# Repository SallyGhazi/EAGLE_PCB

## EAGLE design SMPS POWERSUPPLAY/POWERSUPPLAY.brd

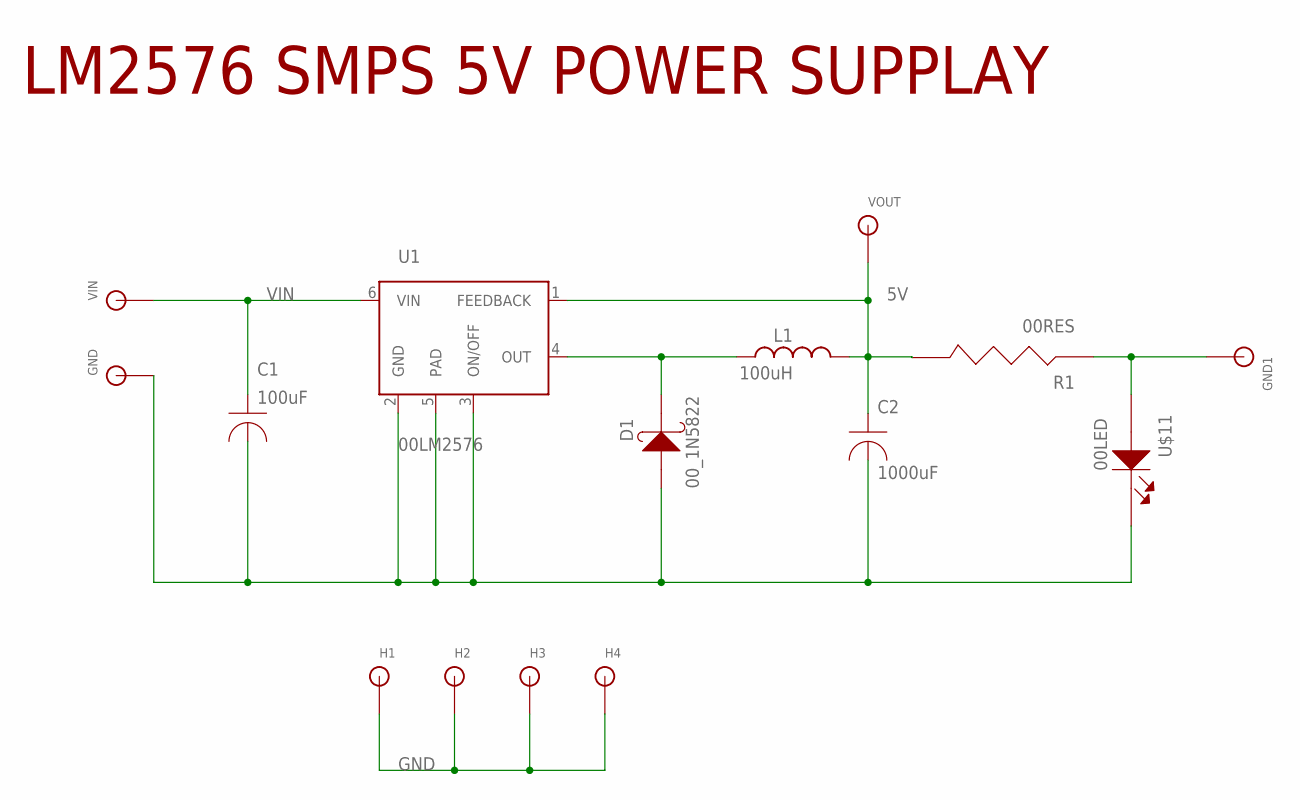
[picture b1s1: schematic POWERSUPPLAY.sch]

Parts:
C1: 100uF; 00CAP
C2: 1000uF; 00CAP
D1: 00_1N5822
GND: 00PAD
GND1: MH_HOLE; 00PAD
H1, H2, H3, H4: MH_HOLE; 00PAD
L1: 100uH; 01INDUCTOR
R1: 00RES
U1: 00LM2576
U$11: 00LED; 0805_LED
VIN: 00PAD
VOUT: MH_HOLE; 00PAD

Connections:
5V: C2.1, L1.2, R1.2, U1.1 (FEEDBACK), VOUT.1
GND: H1.1, H2.1, H3.1, H4.1
unnamed: D1.2, L1.1, U1.4 (OUT)
unnamed: C1.2, C2.2, D1.1, GND.1, U1.2 (GND), U1.3 (ON/OFF), U1.5 (PAD), U$11.2
unnamed: GND1.1, R1.1, U$11.1
VIN: C1.1, U1.6 (VIN), VIN.1

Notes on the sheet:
LM2576 SMPS 5V POWER SUPPLAY

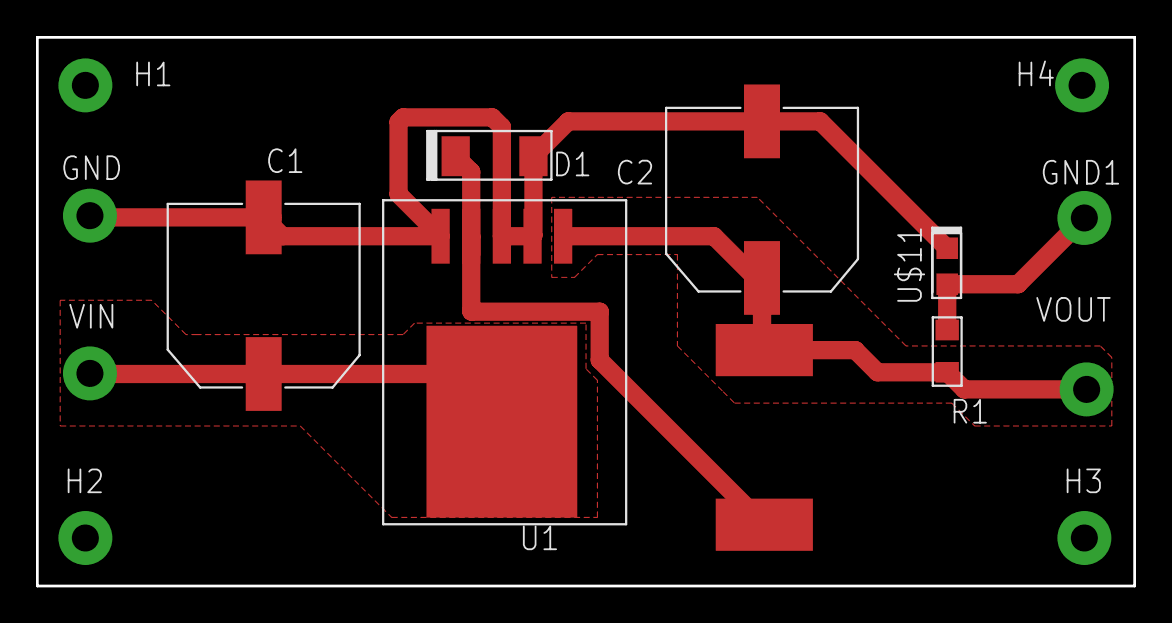
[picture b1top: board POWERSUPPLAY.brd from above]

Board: 2 copper layers, 61.0 x 30.5 mm, 15 parts (0 on the bottom side), 6 nets.
